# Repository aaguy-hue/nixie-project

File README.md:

# Nixie Project
This is a collection of all the PCB designs and software I've written for an STM32-based
Nixie tube clock.

Nixie tubes are some really neat old displays from back during the 1960s, though they kept being
used in the USSR for quite a while, so you can find them on ebay being sold from various
post-soviet states. They have a pretty cool signature orange-ish glow that looks cool, so
I wanted to make a digital clock with them.

Note: Nixies operate at high voltage (albeit very low current), so make sure to exercise caution
when working with them!

<br>

Online image of a Nixie clock (hopefully once mine is built I can replace this image with my own!)

## Project Structure
This is a bit unorganized and will likely soon be refactored, but at the moment this is the structure:
- 3D_Models: 3D models used in the PCBs (the NCH8200HV and my Micro USB connector)
- NixieProject.pretty: Footprint library
- nixies-us.pretty: A footprint library of various Nixie tubes
- nixies-us.mod: Schematic symbols for different Nixie tubes
- Single Tube Board: A PCB to power a single Nixie tube
- software: Software for the various projects
  - nixie_simple: Software for breadboard experiments
  - single_nixie: Software for single Nixie tube PCB
- symbols: Custom schematic symbols

## Part descriptions
- STM32F103C8T6: Microcontroller controlling the tubes
- NCH8200HV: Voltage booster, input 2.5-15V, output 170V
- AMS1117-3.3: 3.3V linear regulator
- K155ID1: BCD-to-decimal decoder

The rest of the parts should be pretty self-explanatory.

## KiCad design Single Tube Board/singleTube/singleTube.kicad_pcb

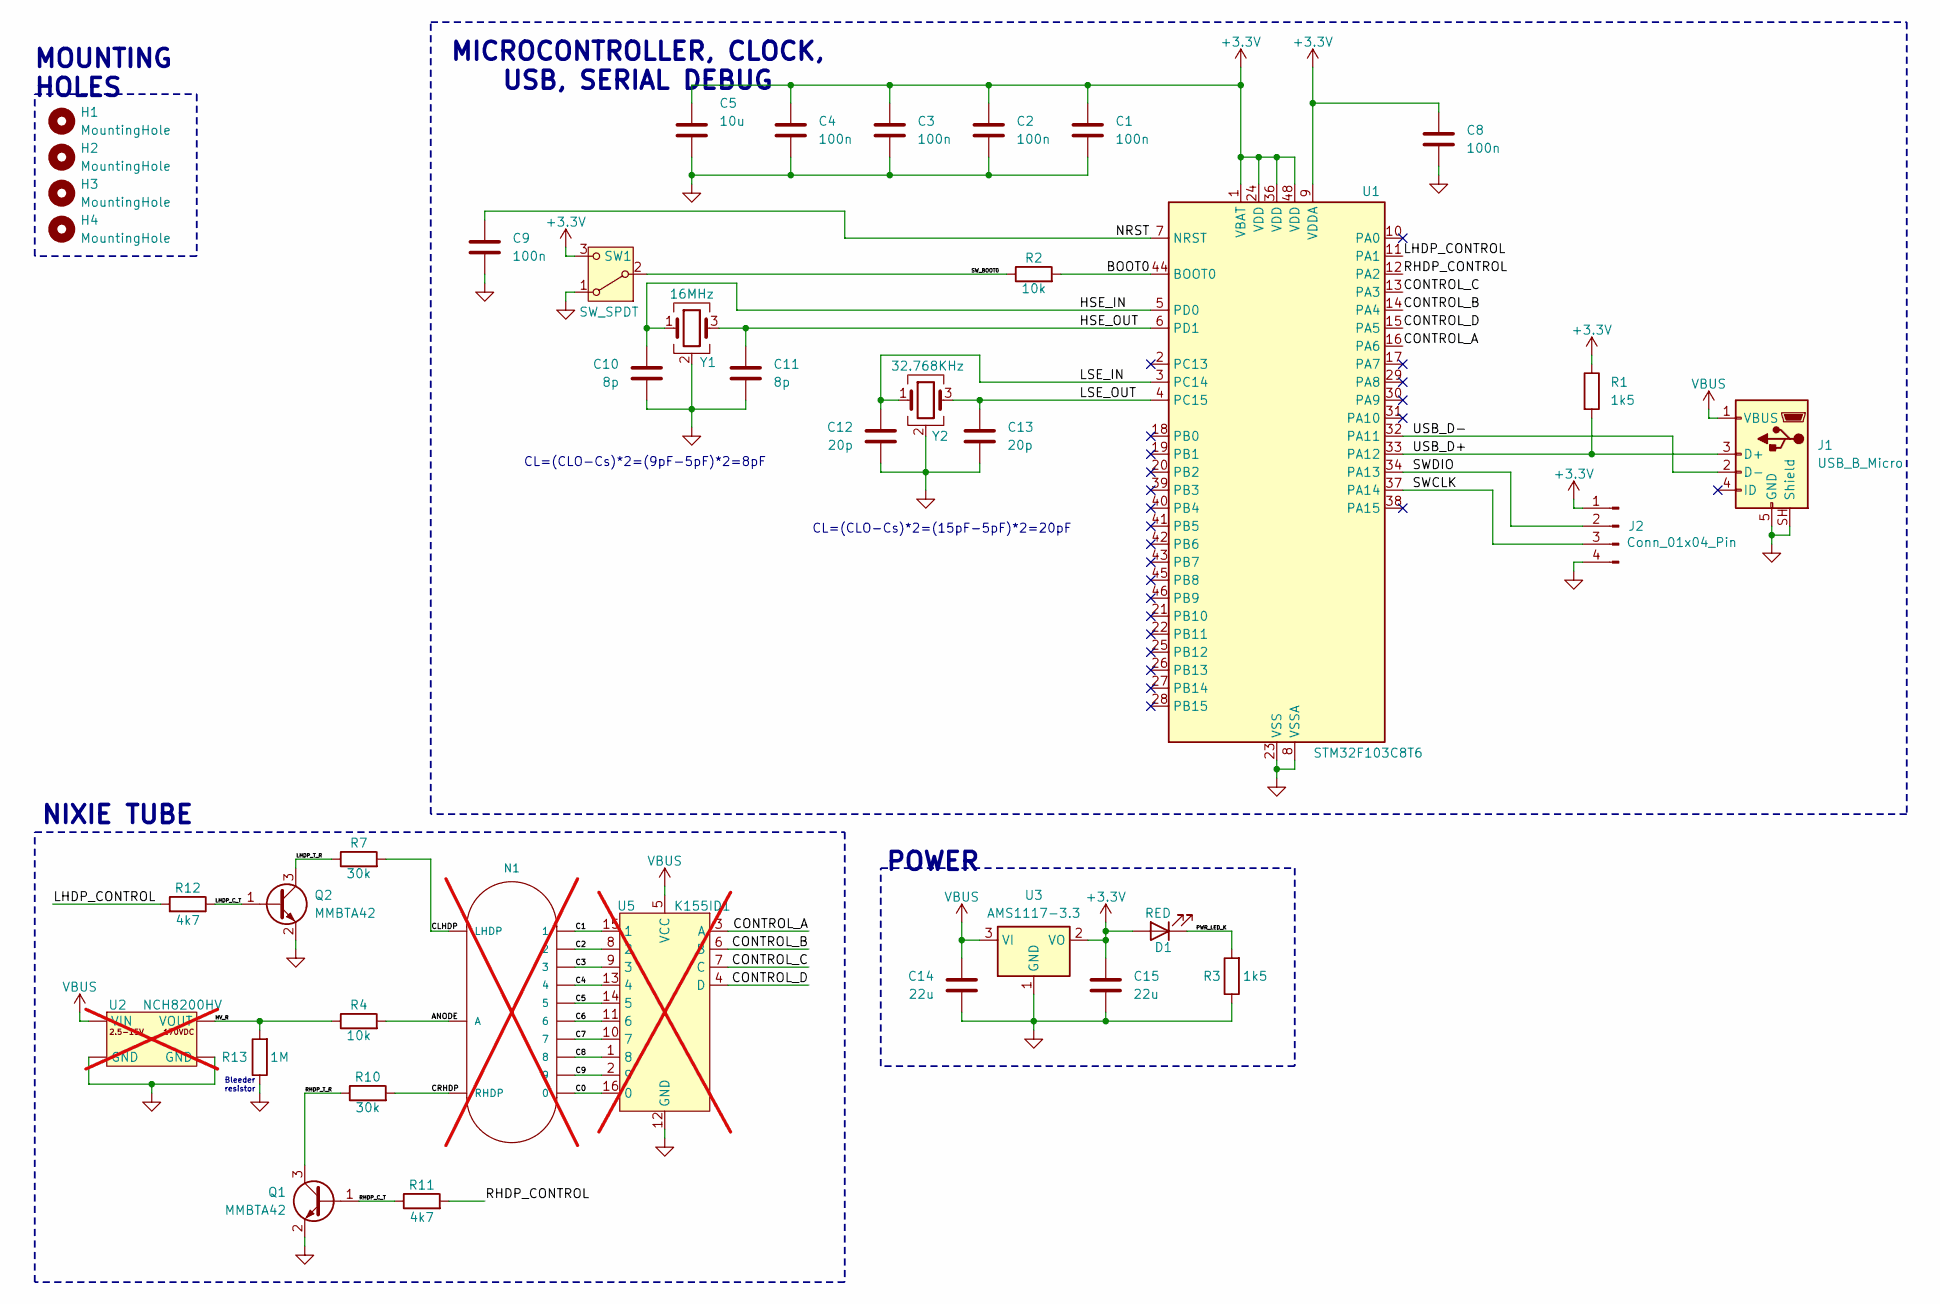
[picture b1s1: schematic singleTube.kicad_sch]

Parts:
C1, C2, C3, C4, C8, C9: 100n; C_0402_1005Metric; JLCPCB Part # C1525
C5: 10u; C_0603_1608Metric; JLCPCB Part # C19702
C10, C11: 8p; C_0402_1005Metric; JLCPCB Part # C1578
C12, C13: 20p; C_0402_1005Metric; JLCPCB Part # C1554
C14, C15: 22u; C_0805_2012Metric; JLCPCB Part # C45783
D1: RED; LED_0603_1608Metric; JLCPCB Part # C2286
H1, H2, H3, H4: MountingHole; MountingHole_3.2mm_M3
J1: USB_B_Micro; USB_Micro-B_XKB_U254-051T-4BH83-F1S; JLCPCB Part # C397452
J2: Conn_01x04_Pin; PinHeader_1x04_P2.54mm_Vertical; JLCPCB Part # C5116483
N1: IN-14; nixies-us-IN-14; not fitted
Q1, Q2: MMBTA42; SOT-23; JLCPCB Part # C118557
R1, R3: 1k5; R_0402_1005Metric; JLCPCB Part # C25867
R2: 10k; R_0402_1005Metric; JLCPCB Part # C25744
R4: 10k; R_1206_3216Metric; JLCPCB Part # C17902
R7, R10: 30k; R_1206_3216Metric; JLCPCB Part # C17999
R11, R12: 4k7; R_1206_3216Metric; JLCPCB Part # C17936
R13: 1M; R_1206_3216Metric; JLCPCB Part # C17927
SW1: SW_SPDT; SW_E-Switch_EG1224_SPDT_Angled; JLCPCB Part # C273395
U1: STM32F103C8T6; LQFP-48_7x7mm_P0.5mm; JLCPCB Part # C8734
U2: NCH8200HV; not fitted
U3: AMS1117-3.3; SOT-223-3_TabPin2; JLCPCB Part # C6186
U5: K155ID1; SN74141N; not fitted
Y1: 16MHz; Crystal_SMD_3225-4Pin_3.2x2.5mm; JLCPCB Part # C13738
Y2: 32.768KHz; Crystal_SMD_2520-4Pin_2.5x2.0mm; JLCPCB Part # C21547573

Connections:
+3.3V: C1.1, C2.1, C3.1, C4.1, C5.1, C8.1, C15.1, D1.2 (A), J2.1, R1.1, SW1.3 (C), U1.1 (VBAT), U1.9 (VDDA), U1.24 (VDD), U1.36 (VDD), U1.48 (VDD), U3.2 (VO)
/ANODE: N1.A, R4.2
/BOOT0: R2.2, U1.44 (BOOT0)
/C0: N1.0, U5.16 (0)
/C1: N1.1, U5.15 (1)
/C2: N1.2, U5.8 (2)
/C3: N1.3, U5.9 (3)
/C4: N1.4, U5.13 (4)
/C5: N1.5, U5.14 (5)
/C6: N1.6, U5.11 (6)
/C7: N1.7, U5.10 (7)
/C8: N1.8, U5.1 (8)
/C9: N1.9, U5.2 (9)
/CLHDP: N1.LHDP, R7.2
/CONTROL_A: U1.16 (PA6), U5.3 (A)
/CONTROL_B: U1.14 (PA4), U5.6 (B)
/CONTROL_C: U1.13 (PA3), U5.7 (C)
/CONTROL_D: U1.15 (PA5), U5.4 (D)
/CRHDP: N1.RHDP, R10.2
/HSE_IN: C10.1, U1.5 (PD0), Y1.1
/HSE_OUT: C11.1, U1.6 (PD1), Y1.3
/HV_R: R4.1, R13.2, U2.2 (VOUT)
/LHDP_CONTROL: R12.2, U1.11 (PA1)
/LHDP_C_T: Q2.1 (B), R12.1
/LHDP_T_R: Q2.3 (C), R7.1
/LSE_IN: C12.1, U1.3 (PC14), Y2.1
/LSE_OUT: C13.1, U1.4 (PC15), Y2.3
/NRST: C9.1, U1.7 (NRST)
/PWR_LED_K: D1.1 (K), R3.2
/RHDP_CONTROL: R11.2, U1.12 (PA2)
/RHDP_C_T: Q1.1 (B), R11.1
/RHDP_T_R: Q1.3 (C), R10.1
/SWCLK: J2.3, U1.37 (PA14)
/SWDIO: J2.2, U1.34 (PA13)
/SW_BOOT0: R2.1, SW1.2 (B)
/USB_D+: J1.3 (D+), R1.2, U1.33 (PA12)
/USB_D-: J1.2 (D-), U1.32 (PA11)
GND: C1.2, C2.2, C3.2, C4.2, C5.2, C8.2, C9.2, C10.2, C11.2, C12.2, C13.2, C14.2, C15.2, J1.5 (GND), J1.SH (Shield), J2.4, Q1.2 (E), Q2.2 (E), R3.1, R13.1, SW1.1 (A), U1.8 (VSSA), U1.23 (VSS), U1.35 (VSS), U1.47 (VSS), U2.3 (GND), U2.4 (GND), U3.1 (GND), U5.12 (GND), Y1.2 (G), Y1.4 (G), Y2.2 (G), Y2.4 (G)
VBUS: C14.1, J1.1 (VBUS), U2.1 (VIN), U3.3 (VI), U5.5 (VCC)

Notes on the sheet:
NIXIE TUBE
MOUNTING HOLES
Bleeder resistor
CL=(CLO-Cs)*2=(9pF-5pF)*2=8pF
CL=(CLO-Cs)*2=(15pF-5pF)*2=20pF
POWER
MICROCONTROLLER, CLOCK, USB, SERIAL DEBUG

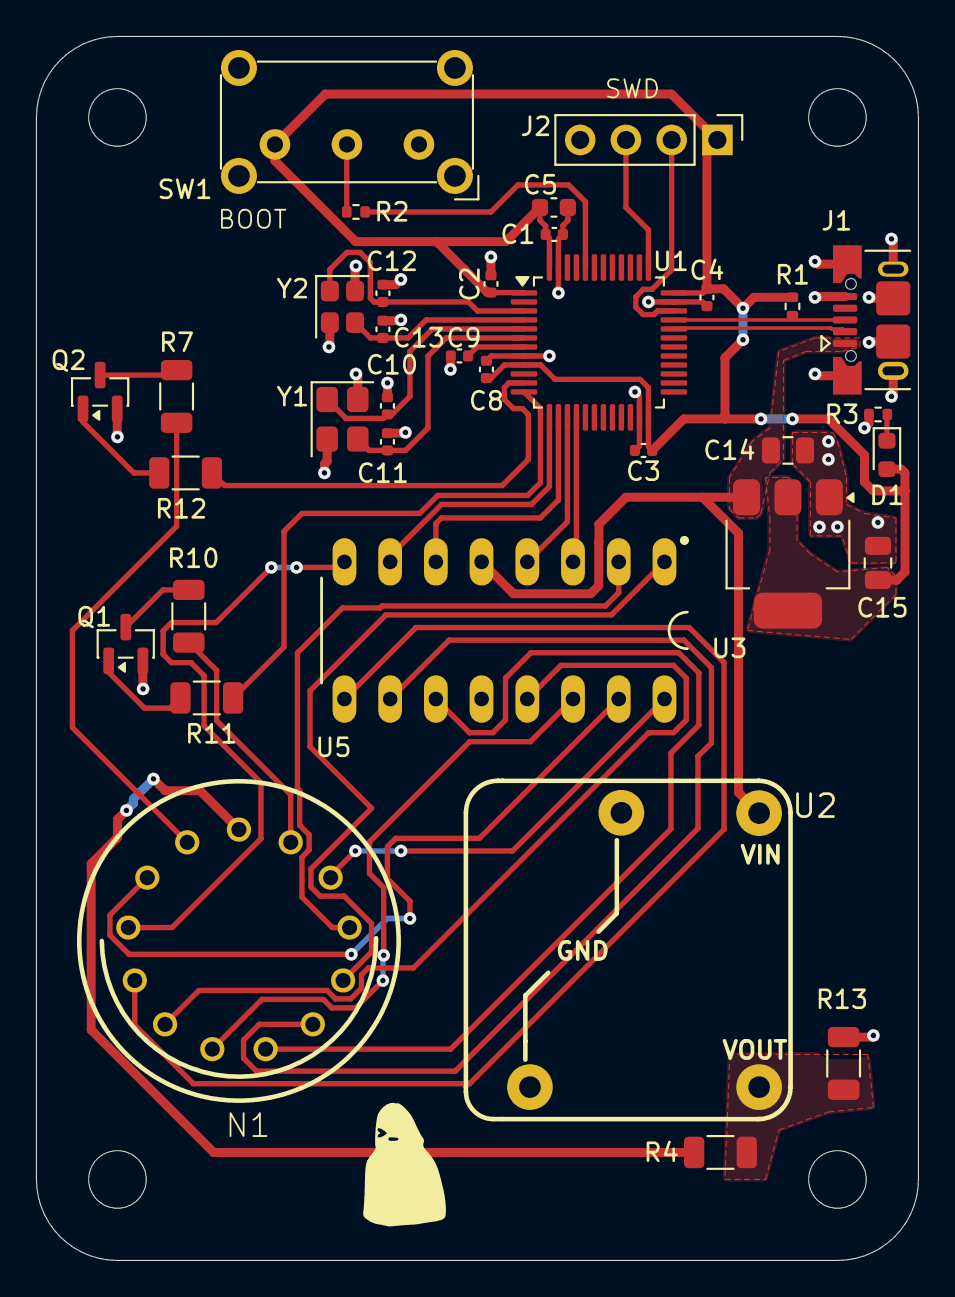
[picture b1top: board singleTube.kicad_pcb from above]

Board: 2 copper layers, 49.0 x 68.0 mm, 39 parts (0 on the bottom side), 39 nets.

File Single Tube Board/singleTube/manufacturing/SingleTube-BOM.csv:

"Comment","Designator","Footprint","JLCPCB Part #"
"8p","C10,C11","Capacitor_SMD:C_0402_1005Metric","C1578"
"20p","C12,C13","Capacitor_SMD:C_0402_1005Metric","C1554"
"100n","C1,C2,C3,C4,C8,C9","Capacitor_SMD:C_0402_1005Metric","C1525"
"10u","C5","Capacitor_SMD:C_0603_1608Metric","C19702"
"22u","C14,C15","Capacitor_SMD:C_0805_2012Metric","C45783"
"1k5","R1,R3","Resistor_SMD:R_0402_1005Metric","C25867"
"4k7","R11,R12","Resistor_SMD:R_1206_3216Metric","C17936"
"10k","R2","Resistor_SMD:R_0402_1005Metric","C25744"
"10k","R4","Resistor_SMD:R_1206_3216Metric","C17902"
"30k","R7,R10","Resistor_SMD:R_1206_3216Metric","C17999"
"32.768KHz","Y2","Crystal:Crystal_SMD_2520-4Pin_2.5x2.0mm","C21547573"
"1M","R13","Resistor_SMD:R_1206_3216Metric","C17927"
"16MHz","Y1","Crystal:Crystal_SMD_3225-4Pin_3.2x2.5mm","C13738"
"AMS1117-3.3","U3","Package_TO_SOT_SMD:SOT-223-3_TabPin2","C6186"
"Conn_01x04_Pin","J2","Connector_PinHeader_2.54mm:PinHeader_1x04_P2.54mm_Vertical","C5116483"
"MMBTA42","Q1,Q2","Package_TO_SOT_SMD:SOT-23","C181172"
"RED","D1","LED_SMD:LED_0603_1608Metric","C2286"
"STM32F103C8T6","U1","Package_QFP:LQFP-48_7x7mm_P0.5mm","C8734"
"SW_SPDT","SW1","Button_Switch_THT:SW_E-Switch_EG1224_SPDT_Angled","C273395"
"USB_B_Micro","J1","Connector_USB:USB_Micro-B_XKB_U254-051T-4BH83-F1S","C397452"
